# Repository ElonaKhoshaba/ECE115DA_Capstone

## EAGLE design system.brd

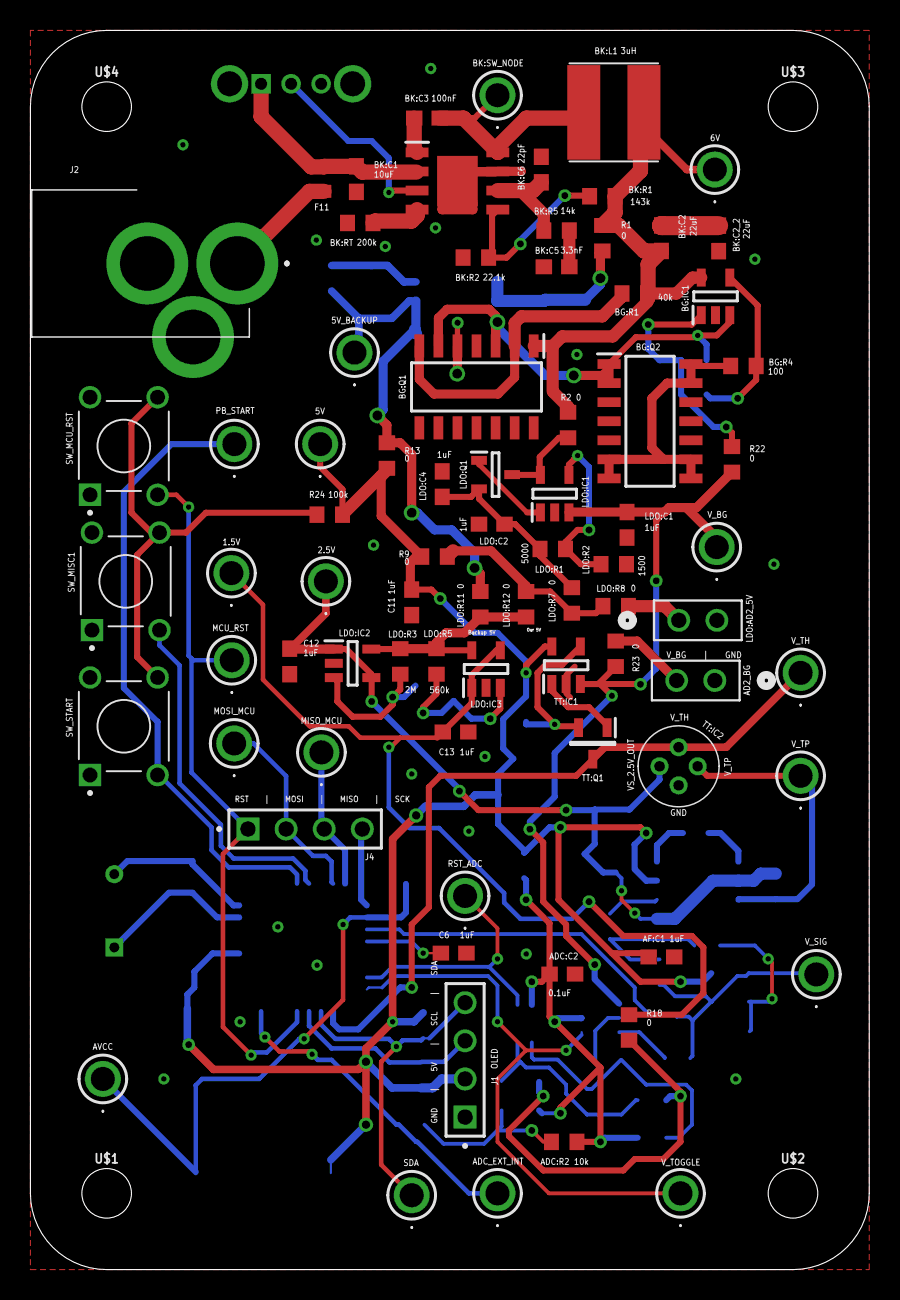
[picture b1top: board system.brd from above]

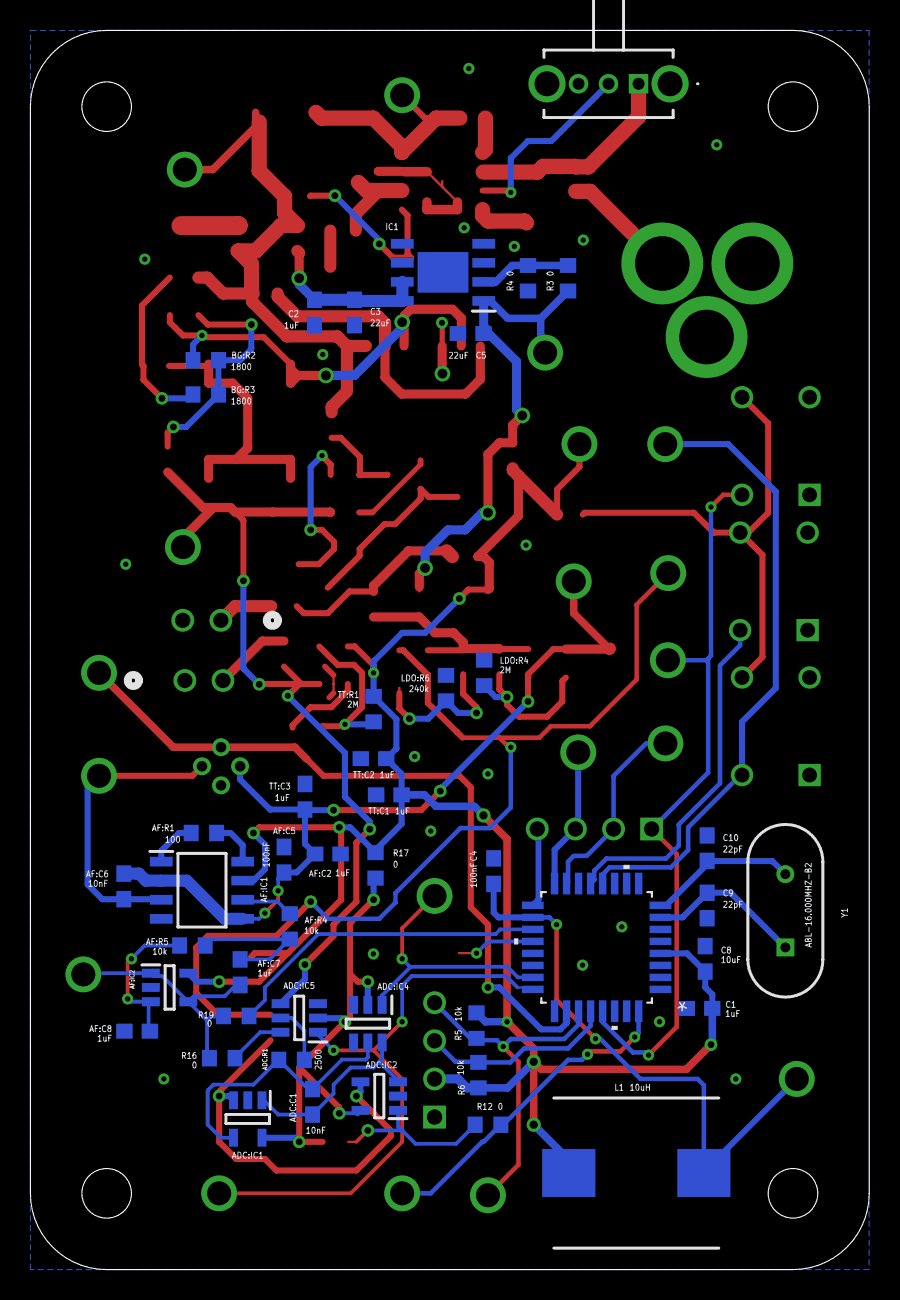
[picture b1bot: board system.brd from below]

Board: 2 copper layers, 55.9 x 82.5 mm, 127 parts (45 on the bottom side), 68 nets.

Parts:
1.5V, 2.5V, 5V, 5V_BACKUP, 6V: 5010
AD2_BG: AD2_BG; CONN_RS1-02-G_ADM
ADC:C1: 10nF; C0603
ADC:C2: 0.1uF; C0603
ADC:IC1: TLV9101IDBVR; SOT95P280X145-5N
ADC:IC2: TLV9021QDBVRQ1; SOT95P280X145-5N
ADC:IC4, ADC:IC5: TMUX1119DBVR; SOT95P280X145-6N
ADC:R1: 2500; R0603
ADC:R2: 10k; R0603
ADC_EXT_INT: 5010
AF:C1, AF:C2, AF:C7, AF:C8: 1uF; C0603
AF:C5: 100nF; C0603
AF:C6: 10nF; C0603
AF:IC1: LT1167CS8-1#PBF; SOIC127P599X175-8N
AF:IC2: TLV9101IDBVR; SOT95P280X145-5N
AF:R1: 100; R0603
AF:R4, AF:R5: 10k; R0603
AVCC: 5010
BG:IC1: TLV9101IDBVR; SOT95P280X145-5N
BG:Q1, BG:Q2: 300S14-U; SOIC127P602X175-14N
BG:R1: 40k; R0603
BG:R2, BG:R3: 1800; R0603
BG:R4: 100; R0603
BK:C1: 10uF; C0603
BK:C2, BK:C2_2: 22uF; C0603
BK:C3: 100nF; C0603
BK:C5: 3.3nF; C0603
BK:C6: 22pF; C0603
BK:IC1: AP64350SP-13; SOIC127P600X163-9N
BK:L1: 3uH; WE-TPC_5818/582892
BK:R1: 143k; R0603
BK:R2: 22.1k; R0603
BK:R5: 14k; R0603
BK:RT: 200k; R0603
BK:S1: SLW-864547-5A-RA-D; SLW8645475ARAD
BK:SW_NODE: 5010
C1, C2, C6, C11, C12, C13: 1uF; C0603
C3, C5: 22uF; C0603
C4: 100nF; C0603
C8: 10uF; C0603
C9, C10: 22pF; C0603
F11: FUSE0603; R0603
IC1: TPS7B8650BQDDARQ1; SOIC127P600X170-9N
J1: OLED; SAMTEC_TSW-104-07-F-S
J2: 163-179PH-EX; 163179PHEX
J4: MCU; SAMTEC_TSW-104-07-F-S
L1: 10uH; INDPM110100X400N
LDO:AD2_5V: RS1-02-G; CONN_RS1-02-G_ADM
LDO:C1, LDO:C2, LDO:C4: 1uF; C0603
LDO:IC1, LDO:IC2, LDO:IC3: TLV9101IDBVR; SOT95P280X145-5N
LDO:Q1: PBSS8110T,215; SOT95P230X110-3N
LDO:R1: 5000; R0603
LDO:R2: 1500; R0603
LDO:R3, LDO:R4: 2M; R0603
LDO:R5: 560k; R0603
LDO:R6: 240k; R0603
LDO:R7, LDO:R8, LDO:R11, LDO:R12: 0; R0603
MCU_RST: 5010
MISO_MCU: 5010
MOSI_MCU: 5010
PB_START: 5010
R1, R2, R3, R4, R9, R12, R13, R16, R17, R18, R19, R22, R23: 0; R0603
R5, R6: 10k; R0603
R24: 100k; R0603
RST_ADC: 5010
SDA: 5010
SW_MCU_RST: 1825910-6; SW_1825910-6-4
SW_MISC1: 1825910-6; SW_1825910-6-4
SW_START: 1825910-6; SW_1825910-6-4
TT:C1, TT:C2, TT:C3: 1uF; C0603
TT:IC1: TLV9101IDBVR; SOT95P280X145-5N
TT:IC2: ZTP-148SRC1; ZTP148SRC1
TT:Q1: FMMT593TC; SOT95P237X112-3N
TT:R1: 2M; R0603
U1: ATMEGA328PB-AU; 32A_MCH
U$1, U$2, U$3, U$4: STAND-OFF
V_BG: 5010
V_SIG: 5010
V_TH: 5010
V_TOGGLE: 5010
V_TP: 5010
Y1: ABL-16.000MHZ-B2; ABL

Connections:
0: AD2_BG.1, ADC:C2.2, ADC:IC1.2, ADC:IC2.2, ADC:IC4.3, ADC:IC5.3, AF:C1.2, AF:C2.2, AF:C5.2, AF:C8.2, AF:IC1.4, AF:IC2.2, BG:IC1.2, BG:Q1.5, BG:Q2.3, BG:Q2.5, BG:Q2.10, BG:Q2.12, BK:C1.2, BK:C2_2.2, BK:C5.2, BK:C6.2, BK:IC1.7, BK:IC1.9, BK:R2.1, BK:RT.1, BK:S1.3, C1.2, C2.2, C3.2, C4.2, C5.2, C6.2, C8.2, C9.1, C10.1, C11.2, C12.2, C13.2, IC1.5, IC1.9, J1.01, J2.B, J2.C, LDO:AD2_5V.2, LDO:C1.2, LDO:C2.2, LDO:C4.2, LDO:IC1.2, LDO:IC2.2, LDO:IC3.2, LDO:R2.1, LDO:R4.1, LDO:R6.1, R4.1, SW_MCU_RST.1, SW_MISC1.1, SW_START.1, TT:C1.2, TT:C2.2, TT:C3.2, TT:IC1.2, TT:IC2.1, U1.5, U1.21
ADC:N$1: ADC:IC5.5, ADC:R1.2
ADC:N$2: ADC:C1.2, ADC:IC1.1, ADC:IC2.3, ADC:IC4.6
ADC:N$4: ADC:C1.1, ADC:IC1.4, ADC:IC4.5, ADC:R1.1
ADC_EXT_INT: ADC_EXT_INT.1, R12.2, U1.32
AF:N$3: AF:IC1.6, AF:R4.1
AF:N$4: AF:IC1.1, AF:R1.1
AF:N$5: AF:IC1.8, AF:R1.2
AF:N$6: AF:C7.1, AF:R4.2, AF:R5.1
AF:N$7: AF:C8.1, AF:IC2.3, AF:R5.2
BG:N$1: BG:Q1.2, BG:Q1.7, BG:R1.1
BG:N$2: BG:IC1.3, BG:Q1.3, BG:Q1.6, BG:Q2.1, BG:Q2.2, BG:R2.1
BG:N$4: BG:IC1.4, BG:R3.1, BG:R4.2
BG:N$5: BG:Q2.6, BG:Q2.7, BG:Q2.8, BG:Q2.9, BG:Q2.13, BG:Q2.14, BG:R4.1
BK:EN: BK:IC1.3, BK:S1.2
BK:N$1: BK:IC1.4, BK:RT.2
BK:N$2: BK:C3.2, BK:IC1.8, BK:L1.1, BK:SW_NODE.1
BK:N$3: BK:C3.1, BK:IC1.1
BK:N$4: BK:C2.2, BK:C2_2.1
BK:N$5: BK:C6.1, BK:IC1.6, BK:R5.2
BK:N$6: BK:IC1.5, BK:R1.1, BK:R2.2
BK:N$7: BK:C5.1, BK:R5.1
EXT_CLK_1: C9.2, U1.7, Y1.1
EXT_CLK_2: C10.2, U1.8, Y1.2
LDO:LS_5V: LDO:IC2.5, LDO:IC3.5, LDO:R3.2, LDO:R5.1, LDO:R11.2, LDO:R12.2
LDO:N$1: LDO:IC1.4, LDO:R1.1, LDO:R2.2
LDO:N$2: LDO:IC2.3, LDO:R3.1, LDO:R4.2
LDO:N$3: LDO:AD2_5V.1, LDO:R8.1
LDO:N$4: LDO:IC1.1, LDO:Q1.1
LDO:N$5: LDO:C2.1, LDO:C4.1, LDO:Q1.2, LDO:R1.2, LDO:R7.1
LDO:N$6: LDO:IC3.3, LDO:R5.2, LDO:R6.2
MCU_RST: J4.01, MCU_RST.1, SW_MCU_RST.3, U1.29
MISO_MCU: J4.03, MISO_MCU.1, U1.16
MOSI_MCU: J4.02, MOSI_MCU.1, U1.15
unnamed: LDO:IC1.5, LDO:Q1.3, R2.2
unnamed: ADC:IC5.6, R16.2
unnamed: F11.1, J2.A
unnamed: AVCC.1, C4.1, L1.1, U1.18
unnamed: ADC:IC1.3, ADC:IC2.4, R18.1
unnamed: ADC:C2.1, ADC:IC1.5, ADC:IC2.5, ADC:IC4.2, ADC:IC5.2, ADC:R2.1, R17.2
unnamed: BG:IC1.1, BG:R2.2, BG:R3.2, R22.1
unnamed: C2.1, C3.1, IC1.7, IC1.8, R1.2
unnamed: IC1.2, R3.1, R4.2
unnamed: AD2_BG.2, R23.1
unnamed: ADC:IC2.1, ADC:R2.2, R12.1
unnamed: C6.1, U1.20
unnamed: R24.1, SW_MCU_RST.4, SW_MISC1.4, SW_START.4
PB_MISC1: SW_MISC1.3, U1.13
PB_START: PB_START.1, SW_START.3, U1.12
RST_ADC: ADC:IC4.1, RST_ADC.1, U1.23
SCK_MCU: J4.04, U1.17
SCL: J1.03, R6.1, U1.28
SDA: J1.04, R5.1, SDA.1, U1.27
TT:N$1: TT:IC1.1, TT:Q1.1
TT:N$3: TT:IC1.4, TT:Q1.2, TT:R1.1
VS_1.5V_OUT: 1.5V.1, C13.1, LDO:IC3.1, LDO:IC3.4, R18.2
VS_2.5V_OUT: 2.5V.1, AF:C2.1, AF:C5.1, AF:C6.2, AF:IC1.2, AF:IC1.5, C12.1, LDO:IC2.1, LDO:IC2.4, TT:C3.1, TT:IC2.3
VS_5V: LDO:R7.2, LDO:R8.2, LDO:R12.1, R9.1
VS_5V_BACKUP: 5V_BACKUP.1, C5.1, IC1.1, LDO:R11.1, R3.2, R13.2
VS_5V_OUT: 5V.1, AF:C1.1, AF:IC1.7, AF:IC2.5, C1.1, C8.1, C11.1, J1.02, L1.2, R5.2, R6.2, R9.2, R13.1, R17.1, R24.2, TT:C1.1, TT:C2.1, TT:IC1.5, TT:R1.2, U1.4
VS_6V: 6V.1, BG:IC1.5, BG:Q1.1, BG:R1.2, BK:C2.1, BK:L1.2, BK:R1.2, R1.1, R2.1
VS_9V: BK:C1.1, BK:IC1.2, BK:S1.1, F11.2
V_BG: ADC:IC5.4, LDO:C1.1, LDO:IC1.3, R22.2, R23.2, TT:IC1.3, V_BG.1
V_SIG: AF:C7.2, AF:IC2.1, AF:IC2.4, R16.1, R19.1, V_SIG.1
V_SIG_ADC: R19.2, U1.19
V_TH: TT:IC2.2, TT:Q1.3, U1.26, V_TH.1
V_TOGGLE: ADC:IC5.1, U1.24, V_TOGGLE.1
V_TP: AF:C6.1, AF:IC1.3, TT:IC2.4, V_TP.1

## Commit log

2024-04-15 inital commit: adding some project files
2024-04-15 added ldo schematic
2024-04-15 Added a bunch of resistors
2024-04-15 Deleted Felipe's Resistor
2024-04-16 finished ldo 6V->5V and level shifter 5V->2.5V
2024-04-16 Unified LDO, level shifter, and buck schematics. Using hierarchical circuit structure with modules abstracting more detailed subcircuits.
2024-04-17 updated TV. pnp, and npn libraries. had wrong footprints
2024-04-17 deleted buck schematic
2024-04-17 finished ldo+lvl shifter. updated buck (not done)
2024-04-18 finished bandgap ref
2024-04-18 Buck Sch and added libraries
2024-04-18 not sure what changed
2024-04-18 changed labels
2024-04-18 Fuse Library
2024-04-18 trying to fix push
2024-04-18 fix?
2024-04-18 thermistor ckt
2024-04-18 adding i/o convention
2024-04-20 adding switch between AD2_5V and VS_5V. added pullups on SCL and SDA lines of MCU
2024-04-20 Create TLV9021QDBVRQ1.lbr
    Adding comparator lmodel
2024-04-20 Added new model and module
    Added filtering module and LT1167 model
2024-04-21 Update system.sch
    Added amplification/filtering and ADC module
2024-04-22 Aesthetic
2024-04-22 Fix some stuff
2024-04-22 added VS_1.5V ref in LDO schematic. cleaned up modules and changed atmega footprint.
2024-04-23 ADC Switch
2024-04-23 Update ADC and MCU wiring
    Finished ADC module
    Wired ADC ports to MCU
    Corrected amplification and filtering module
2024-04-23 cleaned up ports
2024-04-24 adding MCU routing and values for R5 and R6 in LDO
2024-04-24 Added LDO, Changed switches for ADC, added 0 hm R's for power
2024-04-24 Updated R & C to correct model
    Updated all Rs and Cs of ADC and amplifier to 0603
    Added 0 ohm resistors to ADC power supply inputs and routed V_SIG to MCU ADC with a 0 ohm resistor
2024-04-25 added sum stuff to adc wires
2024-04-25 Added mcu connection to adc v_sig and v_th, also added vref stuff and filter lc, need to add footprint for L
2024-04-25 forgot to save
2024-04-25 Removed redundant V_SIG to ADC line
2024-04-25 Fixed warnings
2024-04-25 added footprint for L AVCC
2024-04-26 renamed voltage nets, cleaned up nets and module flow
2024-04-26 renamed parts on main sheet
2024-04-27 validated AMP_AND_FILTER block. fixed wiring on DUAL_SLOPE_ADC
2024-04-28 Added 0 ohm R for V_BG
2024-04-29 push button added
2024-04-29 Create BOMBOY
2024-04-29 Corrected resistor ratio of DC Amp
    Check LDO and voltage refs
2024-04-29 Corrected C6 value for Buck Conv
2024-04-29 Fixed C6 value in Buck Converter
2024-04-29 mcu programming pins
2024-04-30 added testpoints
2024-04-30 created pcb layout
2024-05-01 added cap to 2.5V reference
2024-05-01 connected grounds. added bypass caps to therm/thermopile + amp&filter
2024-05-01 Fixed grounds issue
2024-05-02 Added EXT CLK
    Added an external clock of 16MHz to MCU
2024-05-03 Moved ADC components to bottom right corner
2024-05-03 added caps
2024-05-03 update some stuff
2024-05-04 buck on pcb and renamed modules
2024-05-05 Placed AF section in layout
2024-05-06 Routed ADC and backup LDO
2024-05-06 Updated lvl shifters
    Removed backup level shifters
    Routed backup 5V to each level shifter with a zero ohm resistor.
    Put zero ohm resistor btwn main 5V line and each level shifter.
2024-05-06 changed gnds
2024-05-06 Created mcu source code file
2024-05-06 Revert "pcb"
    This reverts commit 97d68646c3212e804aa7b731d722070677a7e1bc.
2024-05-06 Reapply "pcb"
    This reverts commit c4ffe445a60265340ee5acf139f89f0ad3ef1a34.
2024-05-06 Revert "Merge branch 'main' of https://github.com/ElonaKhoshaba/ECE115DA_Capstone"
    This reverts commit 927025df605e8979b9a531330bf645f60f042d75, reversing
    changes made to 6d04ad174cc823e298dfe0a19fe2da468da60d7b.
2024-05-06 Reapply "Merge branch 'main' of https://github.com/ElonaKhoshaba/ECE115DA_Capstone"
    This reverts commit 5691c949f37dade7db901f6c25ea834ae57e045b.
2024-05-06 fix issue
2024-05-07 changed bat connector. getting .stp files
2024-05-07 added stp files
2024-05-07 added 3d models to libraries
2024-05-07 created 3d model for all libraries. routing
2024-05-07 routing
2024-05-08 Placed AF module on backside of PCB
2024-05-08 made board bigger so sections wip
2024-05-08 Wired ADC and AF parts PCB
2024-05-09 Rerouting ADC and AF
2024-05-09 Wired Power lines to ADC and AF
2024-05-09 finished routing: :q
2024-05-10 fixed airwire errors
2024-05-10 pcb finishing touches
2024-05-10 Fixed small via issue
2024-05-10 screw 3d package
2024-05-10 3d models added for screw (didn't work last time)
2024-05-10 label placement
2024-05-11 fix polygon & added more ground connections
2024-05-12 created gerbers

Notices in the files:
parts and their libraries:
COPYRIGHT: Copyright (C) 2024 Ultra Librarian. All rights reserved.
